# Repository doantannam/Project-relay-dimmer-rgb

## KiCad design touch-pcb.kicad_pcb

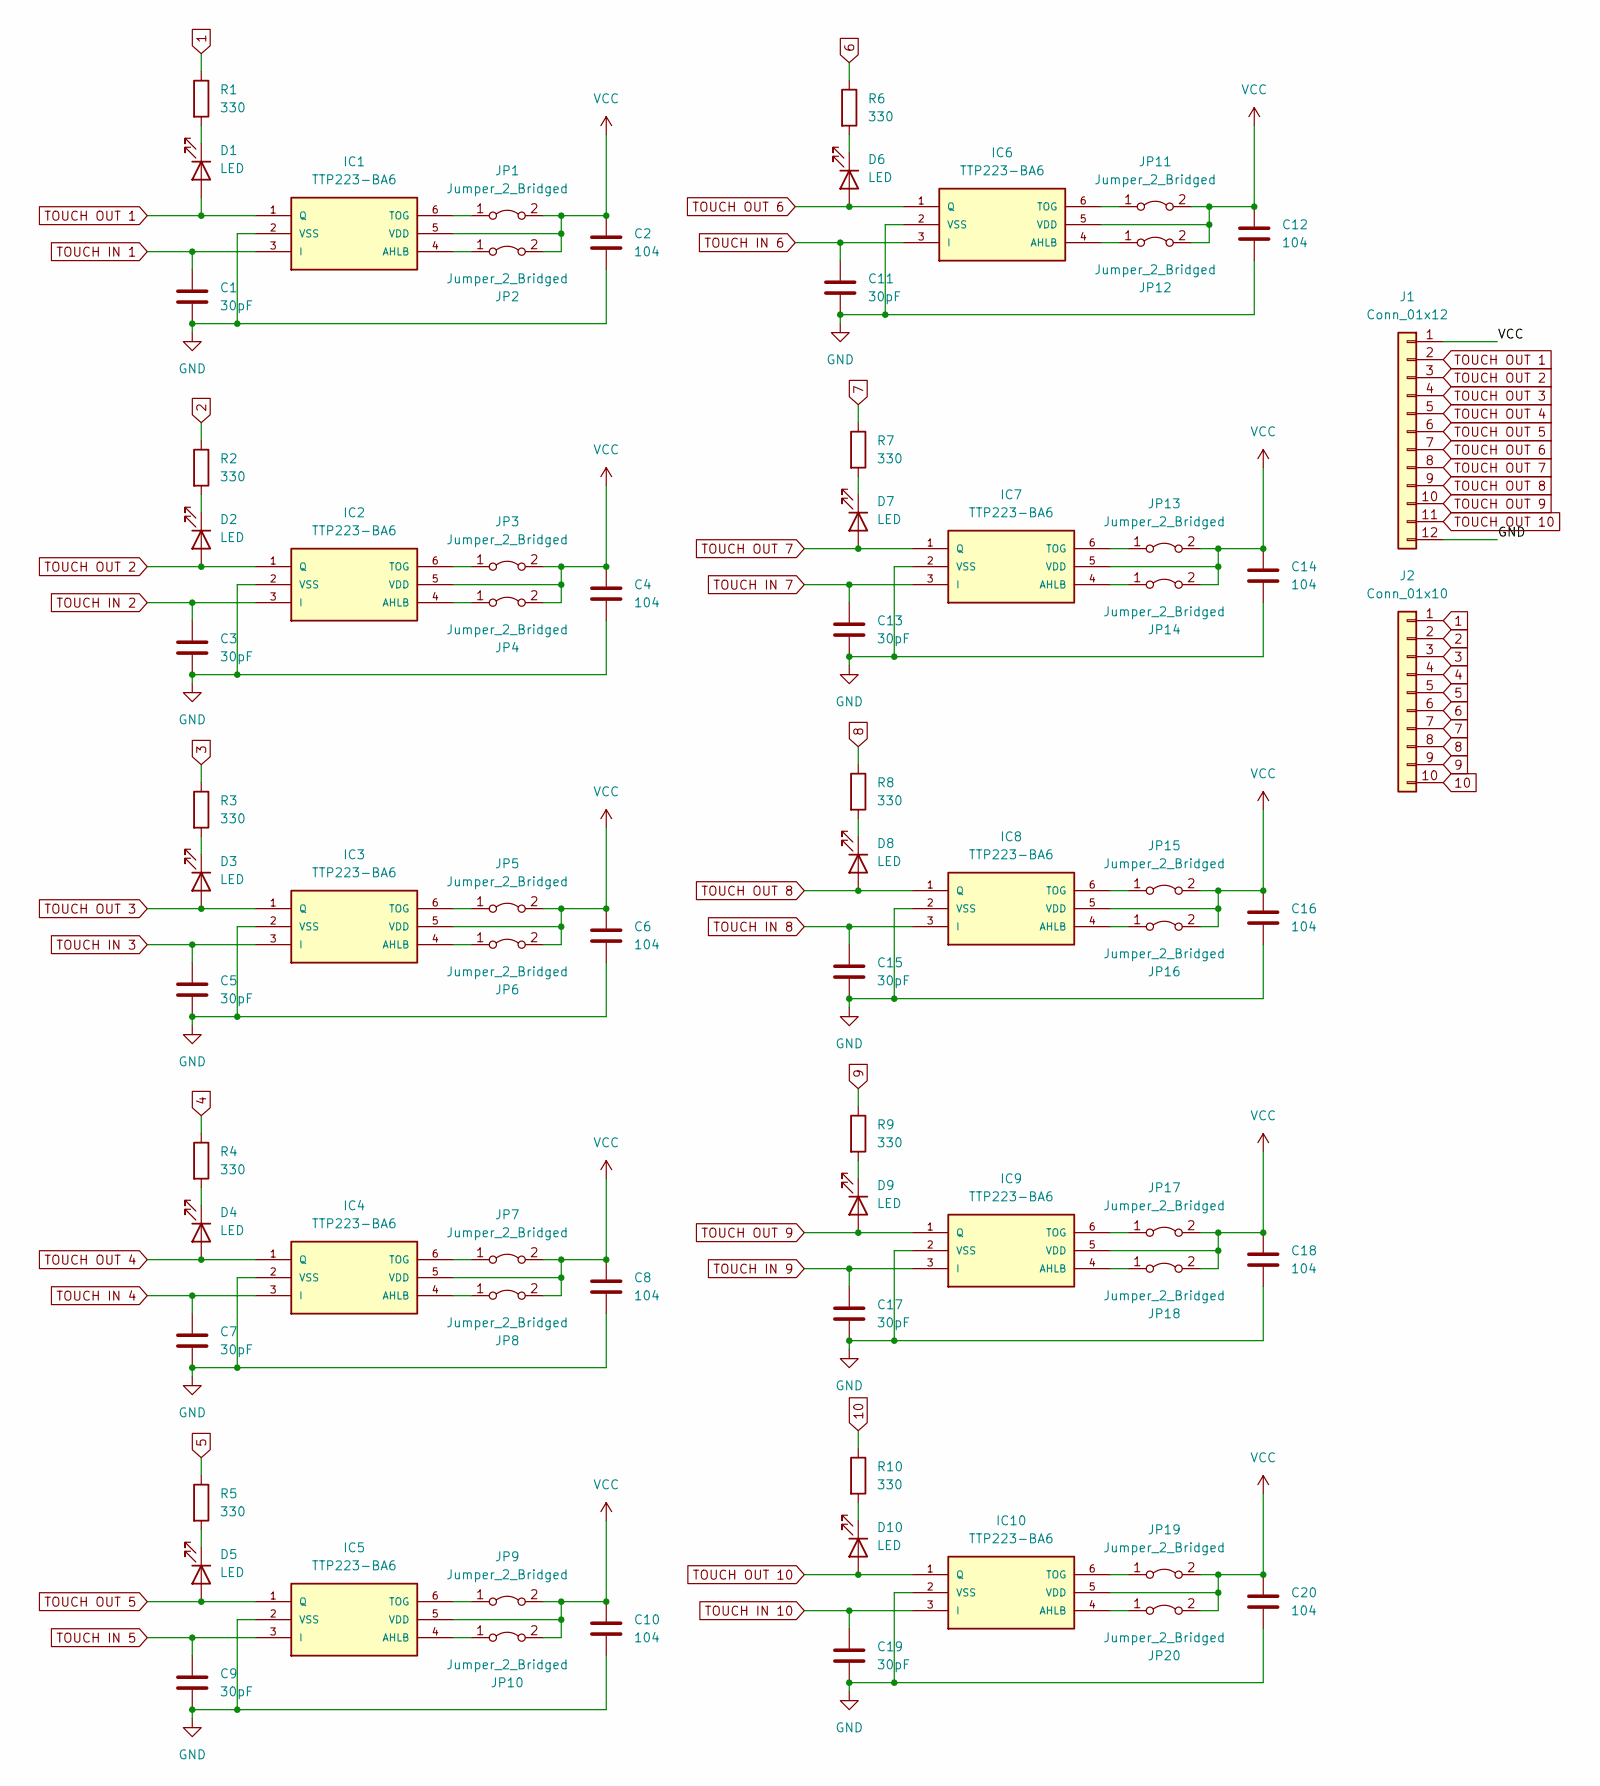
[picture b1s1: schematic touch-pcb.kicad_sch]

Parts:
C1, C3, C5, C7, C9, C11, C13, C15, C17, C19: 30pF; C_0805_2012Metric
C2, C4, C6, C8, C10, C12, C14, C16, C18, C20: 104; C_0805_2012Metric
D1, D2, D3, D4, D5, D6, D7, D8, D9, D10: LED; LED_1206_3216Metric
IC1, IC2, IC3, IC4, IC5, IC6, IC7, IC8, IC9, IC10: TTP223-BA6; SOT95P285X126-6N; MANUFACTURER_PART_NUMBER TTP223-BA6
J1: Conn_01x12; PinHeader_1x12_P2.54mm_Vertical
J2: Conn_01x10; PinHeader_1x10_P2.54mm_Vertical
JP1, JP2, JP3, JP4, JP5, JP6, JP7, JP8, JP9, JP10, JP11, JP12, JP13, JP14, JP15, JP16, JP17, JP18, JP19, JP20: Jumper_2_Bridged; SolderJumper-2_P1.3mm_Bridged2Bar_Pad1.0x1.5mm
R1, R2, R3, R4, R5, R6, R7, R8, R9, R10: 330; R_1206_3216Metric

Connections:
1: J2.1, R1.1
2: J2.2, R2.1
3: J2.3, R3.1
4: J2.4, R4.1
5: J2.5, R5.1
6: J2.6, R6.1
7: J2.7, R7.1
8: J2.8, R8.1
9: J2.9, R9.1
10: J2.10, R10.1
GND: C1.2, C2.2, C3.2, C4.2, C5.2, C6.2, C7.2, C8.2, C9.2, C10.2, C11.2, C12.2, C13.2, C14.2, C15.2, C16.2, C17.2, C18.2, C19.2, C20.2, IC1.2 (VSS), IC2.2 (VSS), IC3.2 (VSS), IC4.2 (VSS), IC5.2 (VSS), IC6.2 (VSS), IC7.2 (VSS), IC8.2 (VSS), IC9.2 (VSS), IC10.2 (VSS), J1.12
unnamed: D8.1 (K), R8.2
unnamed: IC1.4 (AHLB), JP2.1 (A)
unnamed: IC1.6 (TOG), JP1.1 (A)
unnamed: IC2.4 (AHLB), JP4.1 (A)
unnamed: IC2.6 (TOG), JP3.1 (A)
unnamed: IC3.4 (AHLB), JP6.1 (A)
unnamed: IC3.6 (TOG), JP5.1 (A)
unnamed: IC4.4 (AHLB), JP8.1 (A)
unnamed: IC4.6 (TOG), JP7.1 (A)
unnamed: IC5.4 (AHLB), JP10.1 (A)
unnamed: IC5.6 (TOG), JP9.1 (A)
unnamed: IC6.4 (AHLB), JP12.1 (A)
unnamed: IC6.6 (TOG), JP11.1 (A)
unnamed: IC7.4 (AHLB), JP14.1 (A)
unnamed: IC7.6 (TOG), JP13.1 (A)
unnamed: IC8.4 (AHLB), JP16.1 (A)
unnamed: IC8.6 (TOG), JP15.1 (A)
unnamed: IC9.4 (AHLB), JP18.1 (A)
unnamed: IC9.6 (TOG), JP17.1 (A)
unnamed: IC10.4 (AHLB), JP20.1 (A)
unnamed: IC10.6 (TOG), JP19.1 (A)
unnamed: D1.1 (K), R1.2
unnamed: D2.1 (K), R2.2
unnamed: D3.1 (K), R3.2
unnamed: D4.1 (K), R4.2
unnamed: D5.1 (K), R5.2
unnamed: D6.1 (K), R6.2
unnamed: D7.1 (K), R7.2
unnamed: D9.1 (K), R9.2
unnamed: D10.1 (K), R10.2
TOUCH IN 1: C1.1, IC1.3 (I)
TOUCH IN 2: C3.1, IC2.3 (I)
TOUCH IN 3: C5.1, IC3.3 (I)
TOUCH IN 4: C7.1, IC4.3 (I)
TOUCH IN 5: C9.1, IC5.3 (I)
TOUCH IN 6: C11.1, IC6.3 (I)
TOUCH IN 7: C13.1, IC7.3 (I)
TOUCH IN 8: C15.1, IC8.3 (I)
TOUCH IN 9: C17.1, IC9.3 (I)
TOUCH IN 10: C19.1, IC10.3 (I)
TOUCH OUT 1: D1.2 (A), IC1.1 (Q), J1.2
TOUCH OUT 2: D2.2 (A), IC2.1 (Q), J1.3
TOUCH OUT 3: D3.2 (A), IC3.1 (Q), J1.4
TOUCH OUT 4: D4.2 (A), IC4.1 (Q), J1.5
TOUCH OUT 5: D5.2 (A), IC5.1 (Q), J1.6
TOUCH OUT 6: D6.2 (A), IC6.1 (Q), J1.7
TOUCH OUT 7: D7.2 (A), IC7.1 (Q), J1.8
TOUCH OUT 8: D8.2 (A), IC8.1 (Q), J1.9
TOUCH OUT 9: D9.2 (A), IC9.1 (Q), J1.10
TOUCH OUT 10: D10.2 (A), IC10.1 (Q), J1.11
VCC: C2.1, C4.1, C6.1, C8.1, C10.1, C12.1, C14.1, C16.1, C18.1, C20.1, IC1.5 (VDD), IC2.5 (VDD), IC3.5 (VDD), IC4.5 (VDD), IC5.5 (VDD), IC6.5 (VDD), IC7.5 (VDD), IC8.5 (VDD), IC9.5 (VDD), IC10.5 (VDD), J1.1, JP1.2 (B), JP2.2 (B), JP3.2 (B), JP4.2 (B), JP5.2 (B), JP6.2 (B), JP7.2 (B), JP8.2 (B), JP9.2 (B), JP10.2 (B), JP11.2 (B), JP12.2 (B), JP13.2 (B), JP14.2 (B), JP15.2 (B), JP16.2 (B), JP17.2 (B), JP18.2 (B), JP19.2 (B), JP20.2 (B)

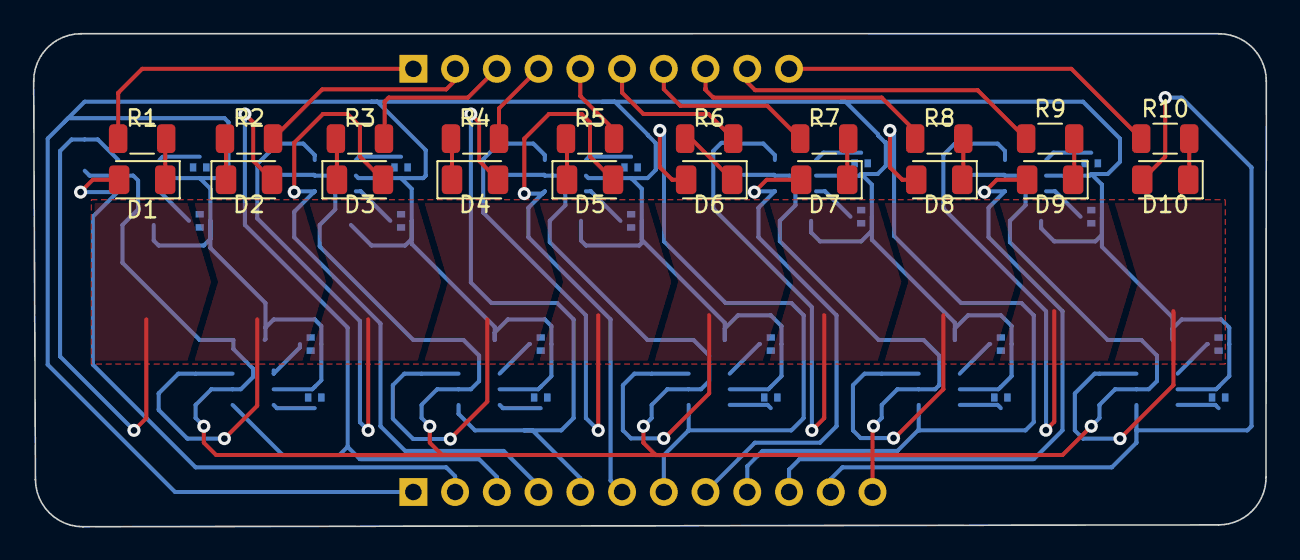
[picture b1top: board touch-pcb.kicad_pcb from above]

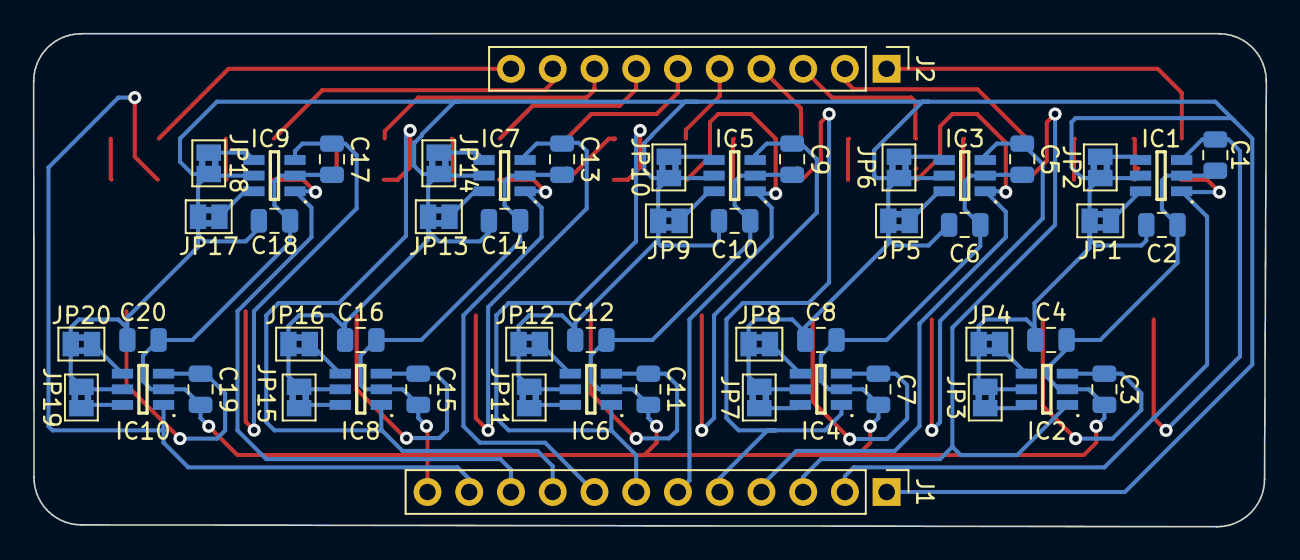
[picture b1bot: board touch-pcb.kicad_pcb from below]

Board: 2 copper layers, 75.0 x 30.0 mm, 72 parts (52 on the bottom side), 62 nets.

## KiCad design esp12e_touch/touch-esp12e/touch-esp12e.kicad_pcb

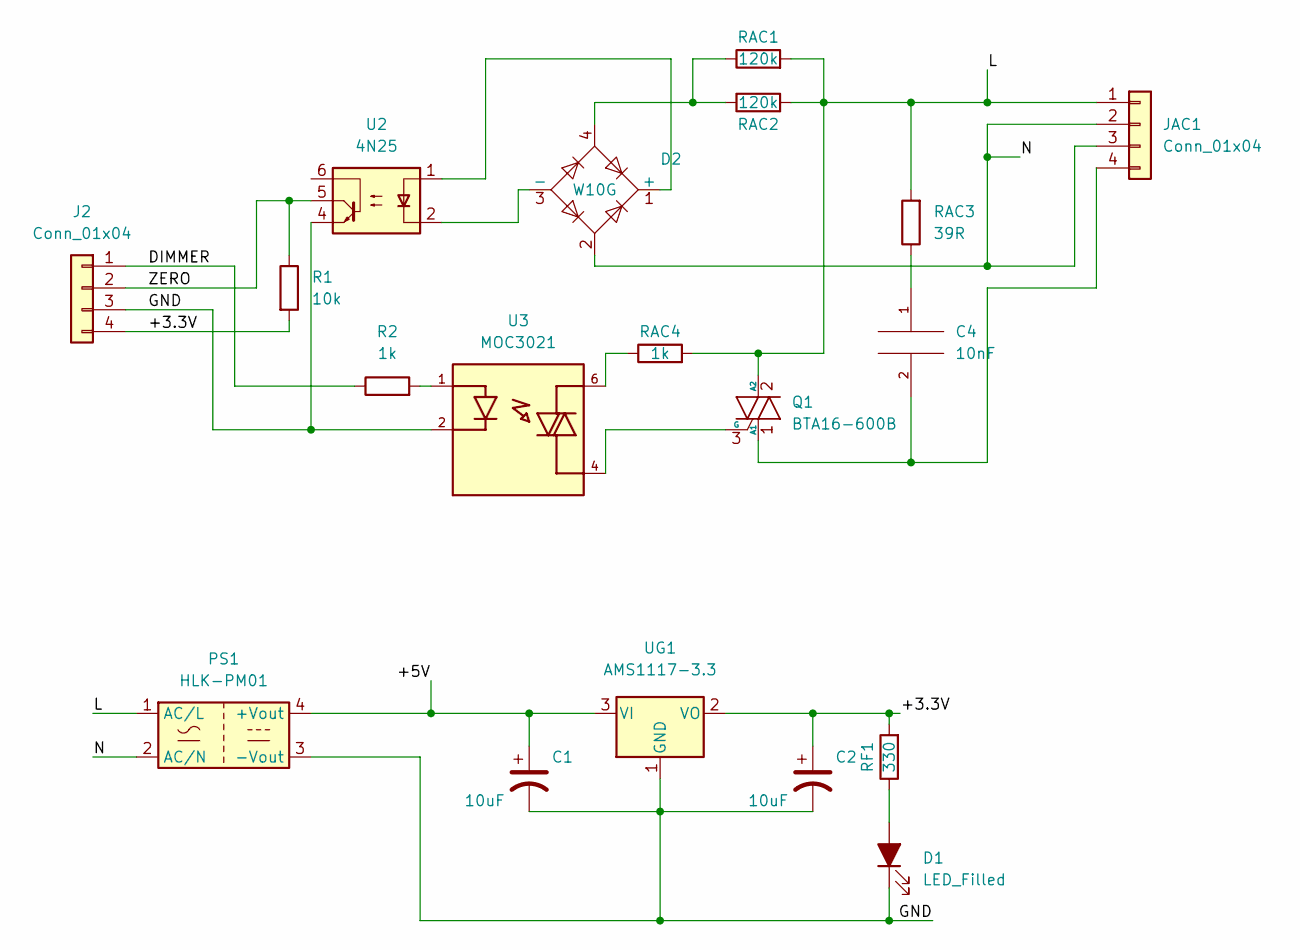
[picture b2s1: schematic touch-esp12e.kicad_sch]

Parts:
C1, C2: 10uF; CP_Radial_D5.0mm_P2.50mm
C4: 10nF; C_Disc_D10.5mm_W5.0mm_P10.00mm
D1: LED_Filled; LED_D3.0mm
D2: W10G; Diode_Bridge_Round_D9.8mm
J2: Conn_01x04; PinSocket_1x04_P2.54mm_Vertical
JAC1: Conn_01x04; SolderWire-2sqmm_1x04_P7.8mm_D2mm_OD3.9mm
PS1: HLK-PM01; Converter_ACDC_HiLink_HLK-PMxx
Q1: BTA16-600B; TO-220-3_Vertical
R1: 10k; R_Axial_DIN0207_L6.3mm_D2.5mm_P7.62mm_Horizontal
R2: 1k; R_Axial_DIN0414_L11.9mm_D4.5mm_P15.24mm_Horizontal
RAC1, RAC2: 120k; R_Axial_DIN0414_L11.9mm_D4.5mm_P15.24mm_Horizontal
RAC3: 39R; R_Axial_DIN0414_L11.9mm_D4.5mm_P15.24mm_Horizontal
RAC4: 1k; R_Axial_DIN0414_L11.9mm_D4.5mm_P15.24mm_Horizontal
RF1: 330; R_Axial_DIN0207_L6.3mm_D2.5mm_P7.62mm_Horizontal
U2: 4N25; DIP-6_W7.62mm
U3: MOC3021; DIP762W45P254L889H508Q6
UG1: AMS1117-3.3; SOT-223-3_TabPin2

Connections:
/+3.3V: C2.1, J2.4, R1.2, RF1.2, UG1.2 (VO)
/+5V: C1.1, PS1.4 (+Vout), UG1.3 (VI)
/DIMMER: J2.1, R2.1
/GND: C1.2, C2.2, D1.1 (K), J2.3, PS1.3 (-Vout), U2.4, U3.2, UG1.1 (GND)
/L: JAC1.1, PS1.1 (AC/L), Q1.2 (A2), RAC1.2, RAC2.2, RAC3.2, RAC4.2
/N: D2.2, JAC1.2, JAC1.3, PS1.2 (AC/N)
/ZERO: J2.2, R1.1, U2.5
unnamed: C4.1, RAC3.1
unnamed: C4.2, JAC1.4, Q1.1 (A1)
unnamed: D1.2 (A), RF1.1
unnamed: D2.1 (+), U2.1
unnamed: D2.3 (-), U2.2
unnamed: D2.4, RAC1.1, RAC2.1
unnamed: Q1.3 (G), U3.4
unnamed: R2.2, U3.1
unnamed: RAC4.1, U3.6

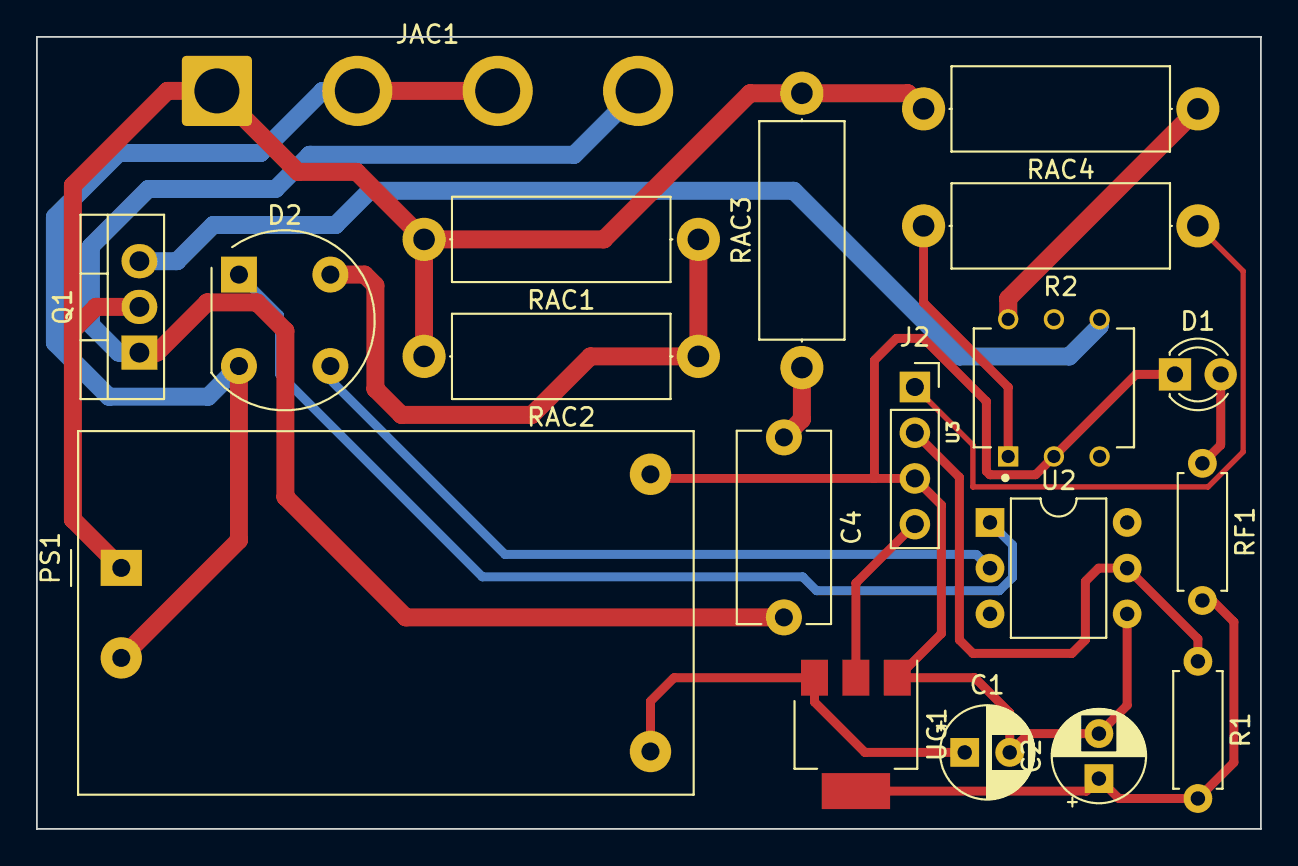
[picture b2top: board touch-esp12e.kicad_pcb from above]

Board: 2 copper layers, 68.0 x 44.0 mm, 19 parts (0 on the bottom side), 16 nets.

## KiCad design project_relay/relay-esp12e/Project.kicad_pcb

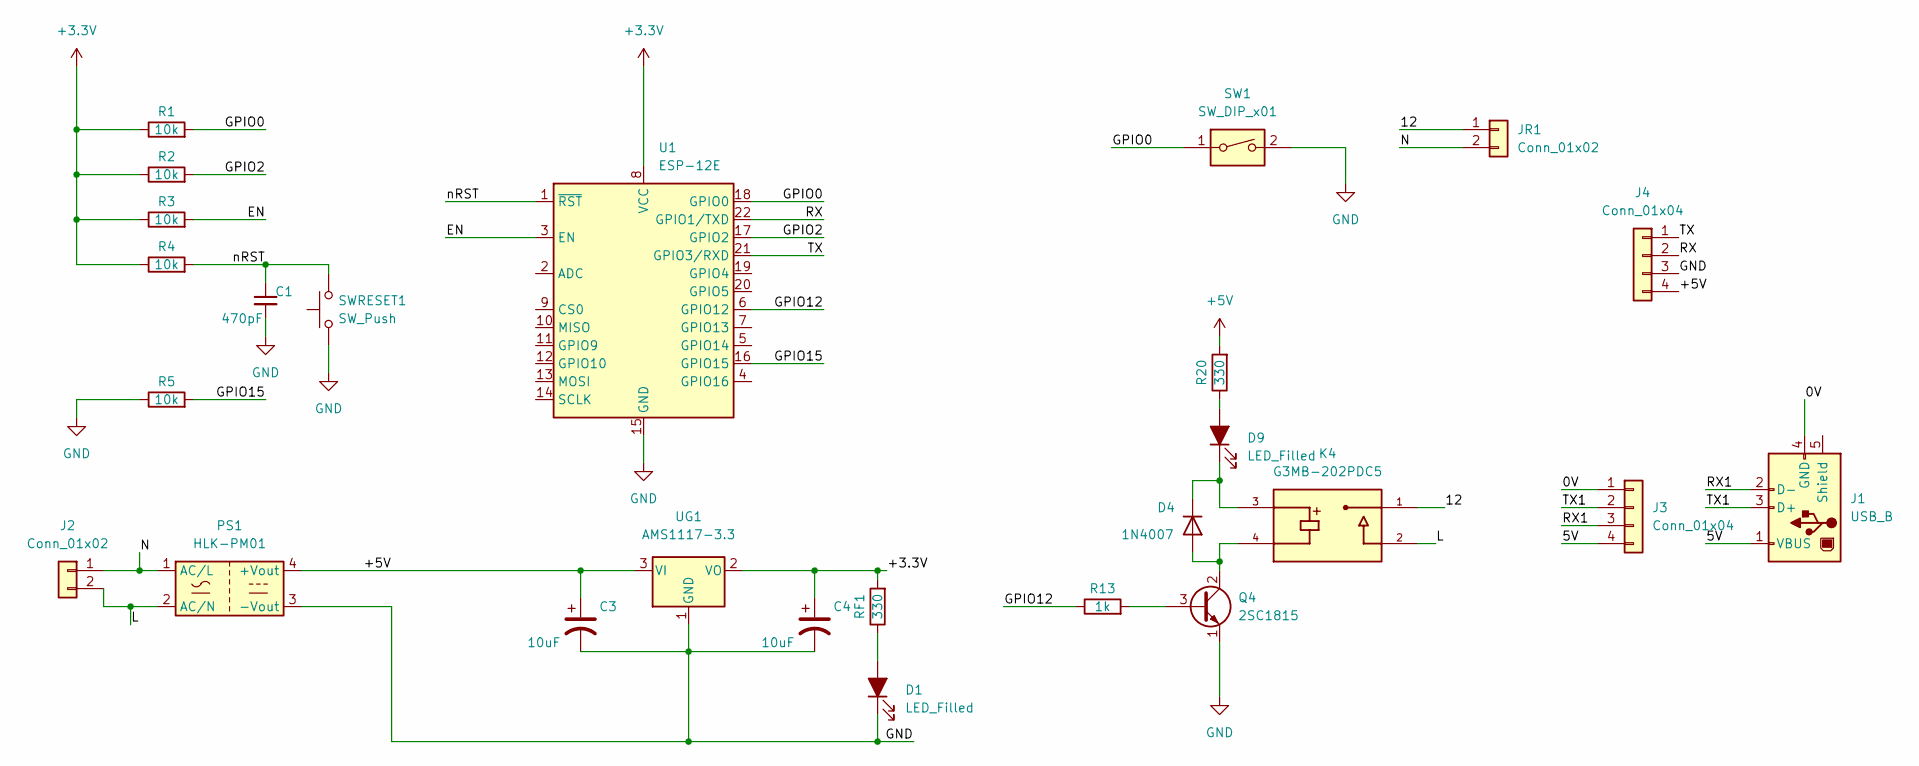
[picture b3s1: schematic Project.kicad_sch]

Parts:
C1: 470pF; C_Disc_D5.0mm_W2.5mm_P5.00mm
C3, C4: 10uF; CP_Radial_D5.0mm_P2.50mm
D1, D9: LED_Filled; LED_D3.0mm
D4: 1N4007; D_DO-41_SOD81_P10.16mm_Horizontal
J1: USB_B; USB_B_Lumberg_2411_02_Horizontal
J2: Conn_01x02; PhoenixContact_MC_1,5_2-G-3.81_1x02_P3.81mm_Horizontal
J3, J4: Conn_01x04; PinSocket_1x04_P2.54mm_Vertical
JR1: Conn_01x02; PhoenixContact_MC_1,5_2-G-3.81_1x02_P3.81mm_Horizontal
K4: G3MB-202PDC5; RELAY_G3MB-202PDC5; PARTREV J091-E1-1A
PS1: HLK-PM01; Converter_ACDC_HiLink_HLK-PMxx
Q4: 2SC1815; TO-92_Inline
R1, R2, R3, R4, R5: 10k; R_Axial_DIN0207_L6.3mm_D2.5mm_P10.16mm_Horizontal
R13: 1k; R_Axial_DIN0207_L6.3mm_D2.5mm_P10.16mm_Horizontal
R20: 330; R_Axial_DIN0207_L6.3mm_D2.5mm_P10.16mm_Horizontal
RF1: 330; R_Axial_DIN0207_L6.3mm_D2.5mm_P10.16mm_Horizontal
SW1: SW_DIP_x01; PinHeader_1x02_P2.54mm_Vertical
SWRESET1: SW_Push; SW_Tactile_SPST_Angled_PTS645Vx39-2LFS
U1: ESP-12E
UG1: AMS1117-3.3; SOT-223-3_TabPin2

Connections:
+3.3V: C4.1, R1.1, R2.1, R3.1, R4.1, RF1.2, U1.8 (VCC), UG1.2 (VO)
+5V: C3.1, J4.4, PS1.4 (+Vout), R20.2, UG1.3 (VI)
/0V: J1.4 (GND), J3.1
/5V: J1.1 (VBUS), J3.4
/12: JR1.1, K4.1
/EN: R3.2, U1.3 (EN)
/GPIO0: R1.2, SW1.1, U1.18 (GPIO0)
/GPIO2: R2.2, U1.17 (GPIO2)
/GPIO12: R13.1, U1.6 (GPIO12)
/GPIO15: R5.2, U1.16 (GPIO15)
/L: J2.2, K4.2, PS1.2 (AC/N)
/N: J2.1, JR1.2, PS1.1 (AC/L)
/RX: J4.2, U1.22 (GPIO1/TXD)
/RX1: J1.2 (D-), J3.3
/TX: J4.1, U1.21 (GPIO3/RXD)
/TX1: J1.3 (D+), J3.2
/nRST: C1.1, R4.2, SWRESET1.1, U1.1 (~RST)
GND: C1.2, C3.2, C4.2, D1.1 (K), J4.3, PS1.3 (-Vout), Q4.1 (E), R5.1, SW1.2, SWRESET1.2, U1.15 (GND), UG1.1 (GND)
unnamed: D1.2 (A), RF1.1
unnamed: D4.1 (K), D9.1 (K), K4.3
unnamed: D4.2 (A), K4.4, Q4.2 (C)
unnamed: D9.2 (A), R20.1
unnamed: Q4.3 (B), R13.2

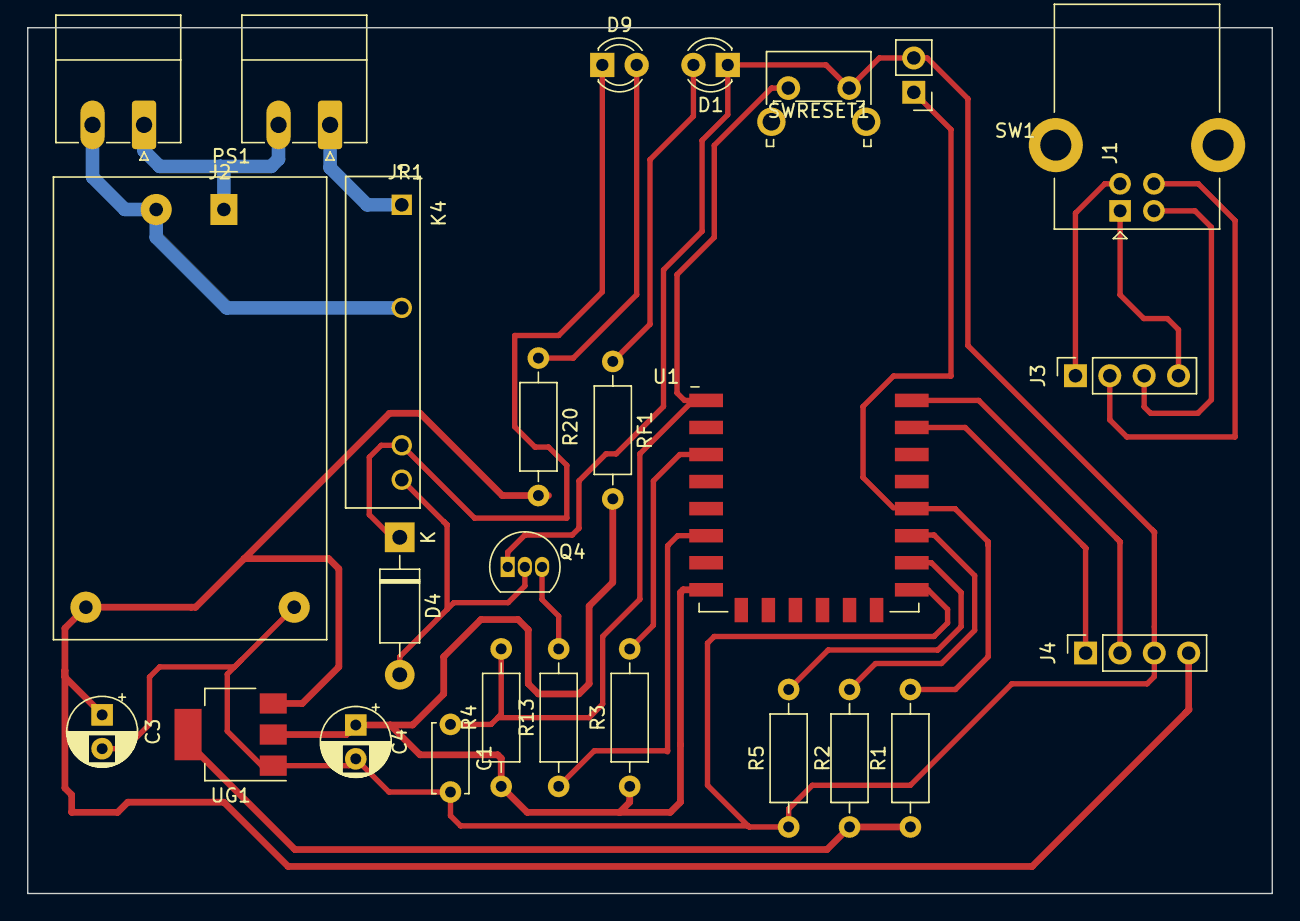
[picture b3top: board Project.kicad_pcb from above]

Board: 2 copper layers, 92.0 x 64.0 mm, 26 parts (0 on the bottom side), 23 nets.

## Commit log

2022-12-28 create project
2022-12-29 pcb touch
2022-12-29 touch new
2022-12-30 file touch new
2023-02-16 new-socket
2023-03-03 new-pcb
